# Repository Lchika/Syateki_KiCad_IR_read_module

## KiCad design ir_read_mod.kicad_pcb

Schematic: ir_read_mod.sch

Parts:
D1, D2, D3, D4: LED; LED_0603_1608Metric_Castellated
J2: Conn_01x05_Female; PinSocket_1x05_P2.54mm_Vertical
J3: Conn_01x04_Female; PinSocket_1x04_P2.54mm_Vertical
Q1: Q_Photo_NPN; LED_D5.0mm
R1, R2, R3, R4, R5, R6, R7: 10k; R_0805_2012Metric_Pad1.15x1.40mm_HandSolder
R8, R9, R10, R11: 300; R_0603_1608Metric_Pad1.05x0.95mm_HandSolder
RV1: R_POT; Potentiometer_ACP_CA9-H5_Horizontal
SW1: SW_Coded_SH-7070; Nidec_Copal_SH-7010C
SW2: SW_SPDT; PinHeader_1x03_P2.54mm_Vertical
U1: PIC16F1503-IP; DIP-14_W7.62mm

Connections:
+5V: J2.2, J3.1, Q1.1, R5.2, R6.1, R7.1, SW1.C, U1.1
GND: D1.1, D2.1, D3.1, D4.1, J2.3, J3.2, R1.1, R2.1, R3.1, R4.1, RV1.2, U1.14
unnamed: D1.2, R8.2
unnamed: D2.2, R9.2
unnamed: D3.2, R10.2
unnamed: D4.2, R11.2
unnamed: J2.1, SW2.2, U1.4
unnamed: J2.4, R1.2, SW1.1, U1.13
unnamed: J2.5, R2.2, SW1.2, U1.12
unnamed: J3.3, R7.2, U1.10
unnamed: J3.4, R6.2, U1.9
unnamed: Q1.2, RV1.1, U1.8
unnamed: R5.1, SW2.3
unnamed: R8.1, U1.11
unnamed: R9.1, U1.3
unnamed: R10.1, U1.2
unnamed: R11.1, U1.6
RC3: R3.2, SW1.4, U1.7
RC5: R4.2, SW1.8, U1.5

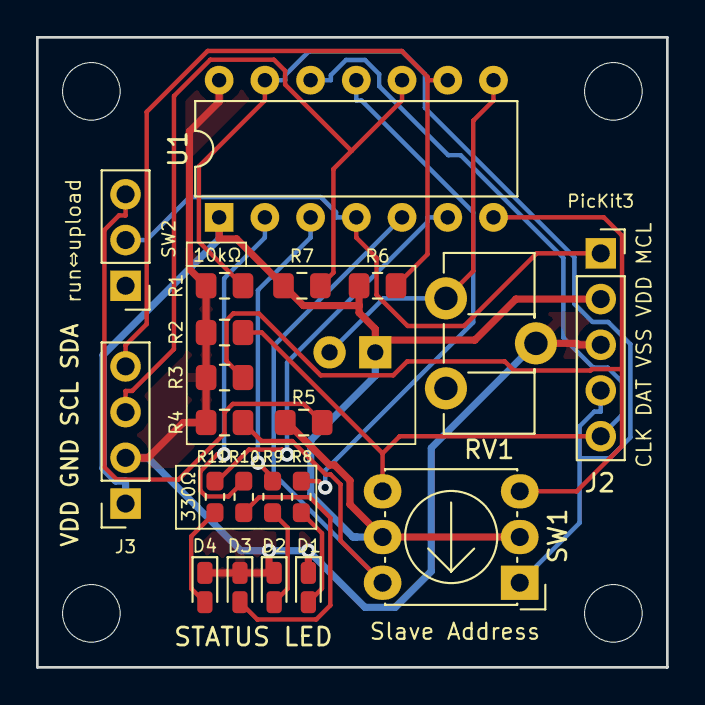
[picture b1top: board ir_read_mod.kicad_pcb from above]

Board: 2 copper layers, 35.0 x 35.0 mm, 26 parts (1 on the bottom side), 19 nets.

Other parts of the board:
hole1, hole2, hole3, hole4: MountingHole_3.2mm_M3

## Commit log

2019-10-05 Update: fix parts
